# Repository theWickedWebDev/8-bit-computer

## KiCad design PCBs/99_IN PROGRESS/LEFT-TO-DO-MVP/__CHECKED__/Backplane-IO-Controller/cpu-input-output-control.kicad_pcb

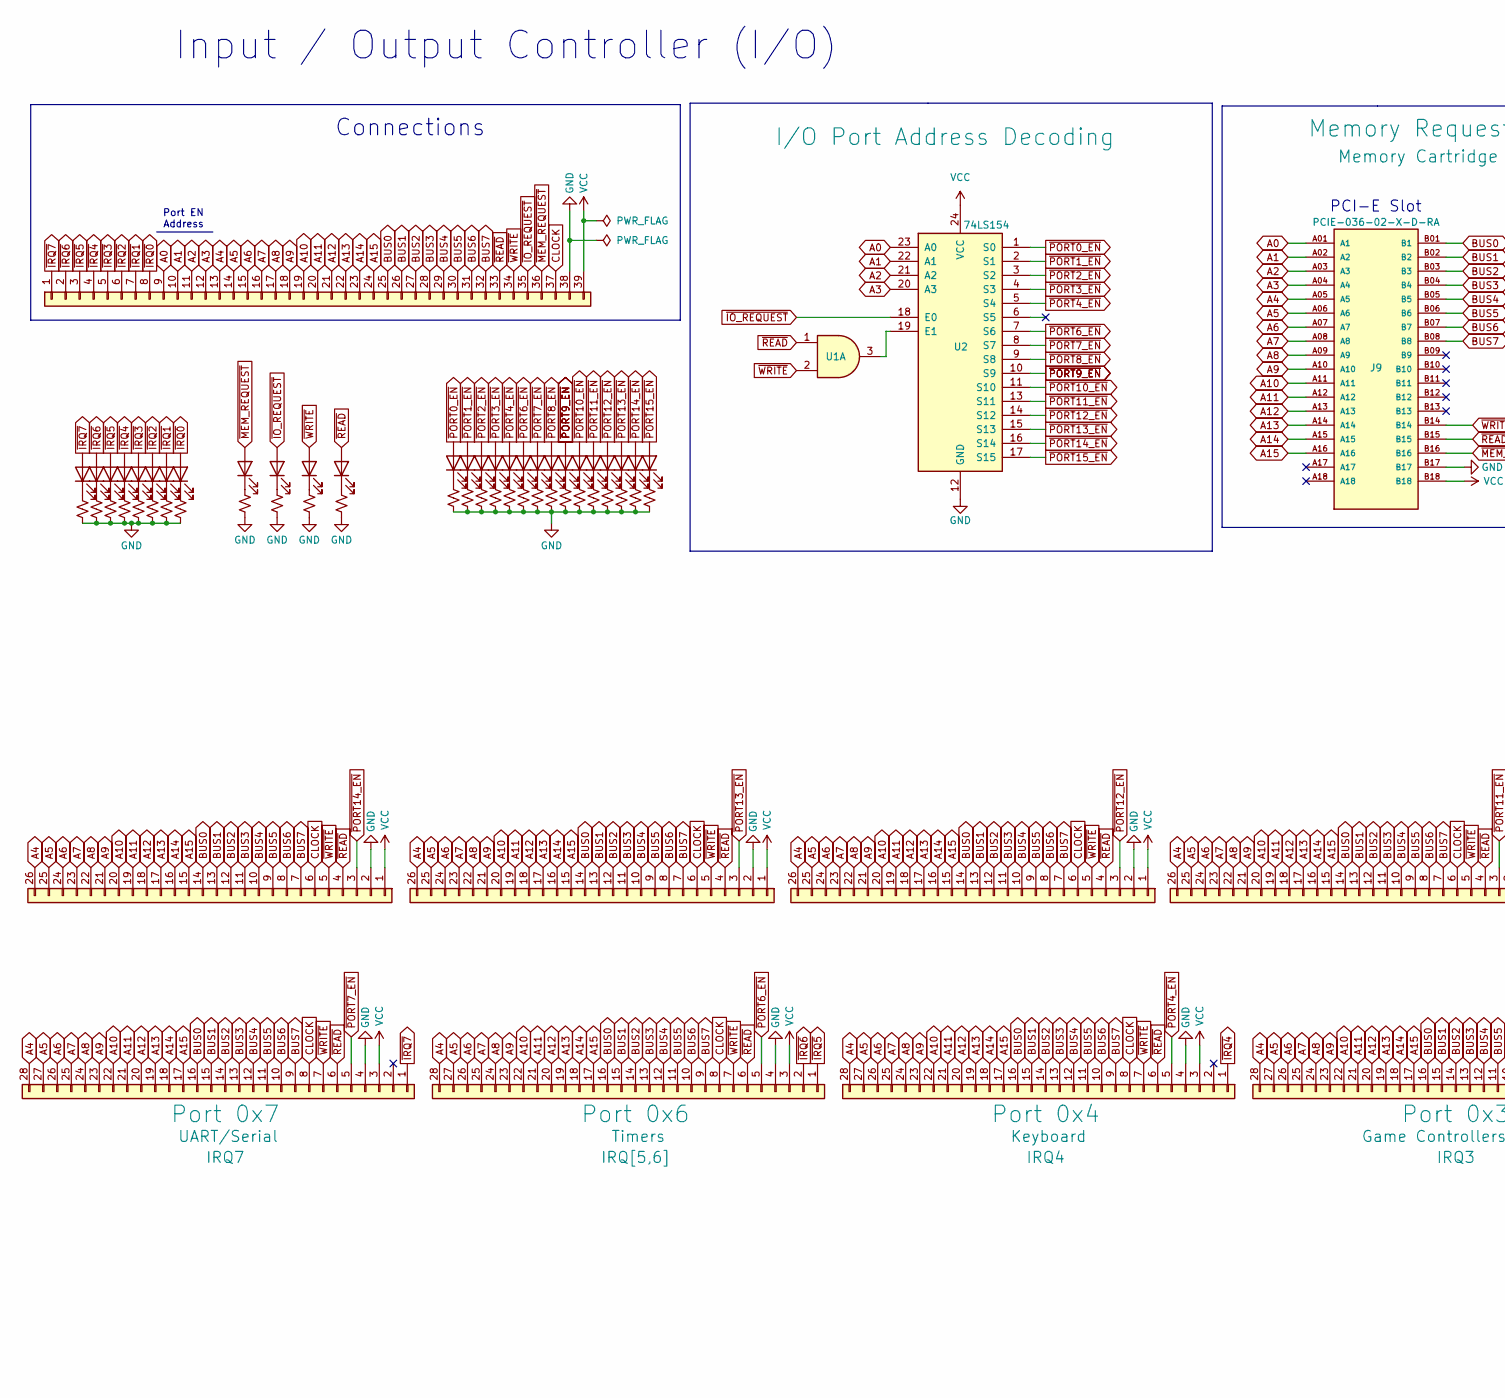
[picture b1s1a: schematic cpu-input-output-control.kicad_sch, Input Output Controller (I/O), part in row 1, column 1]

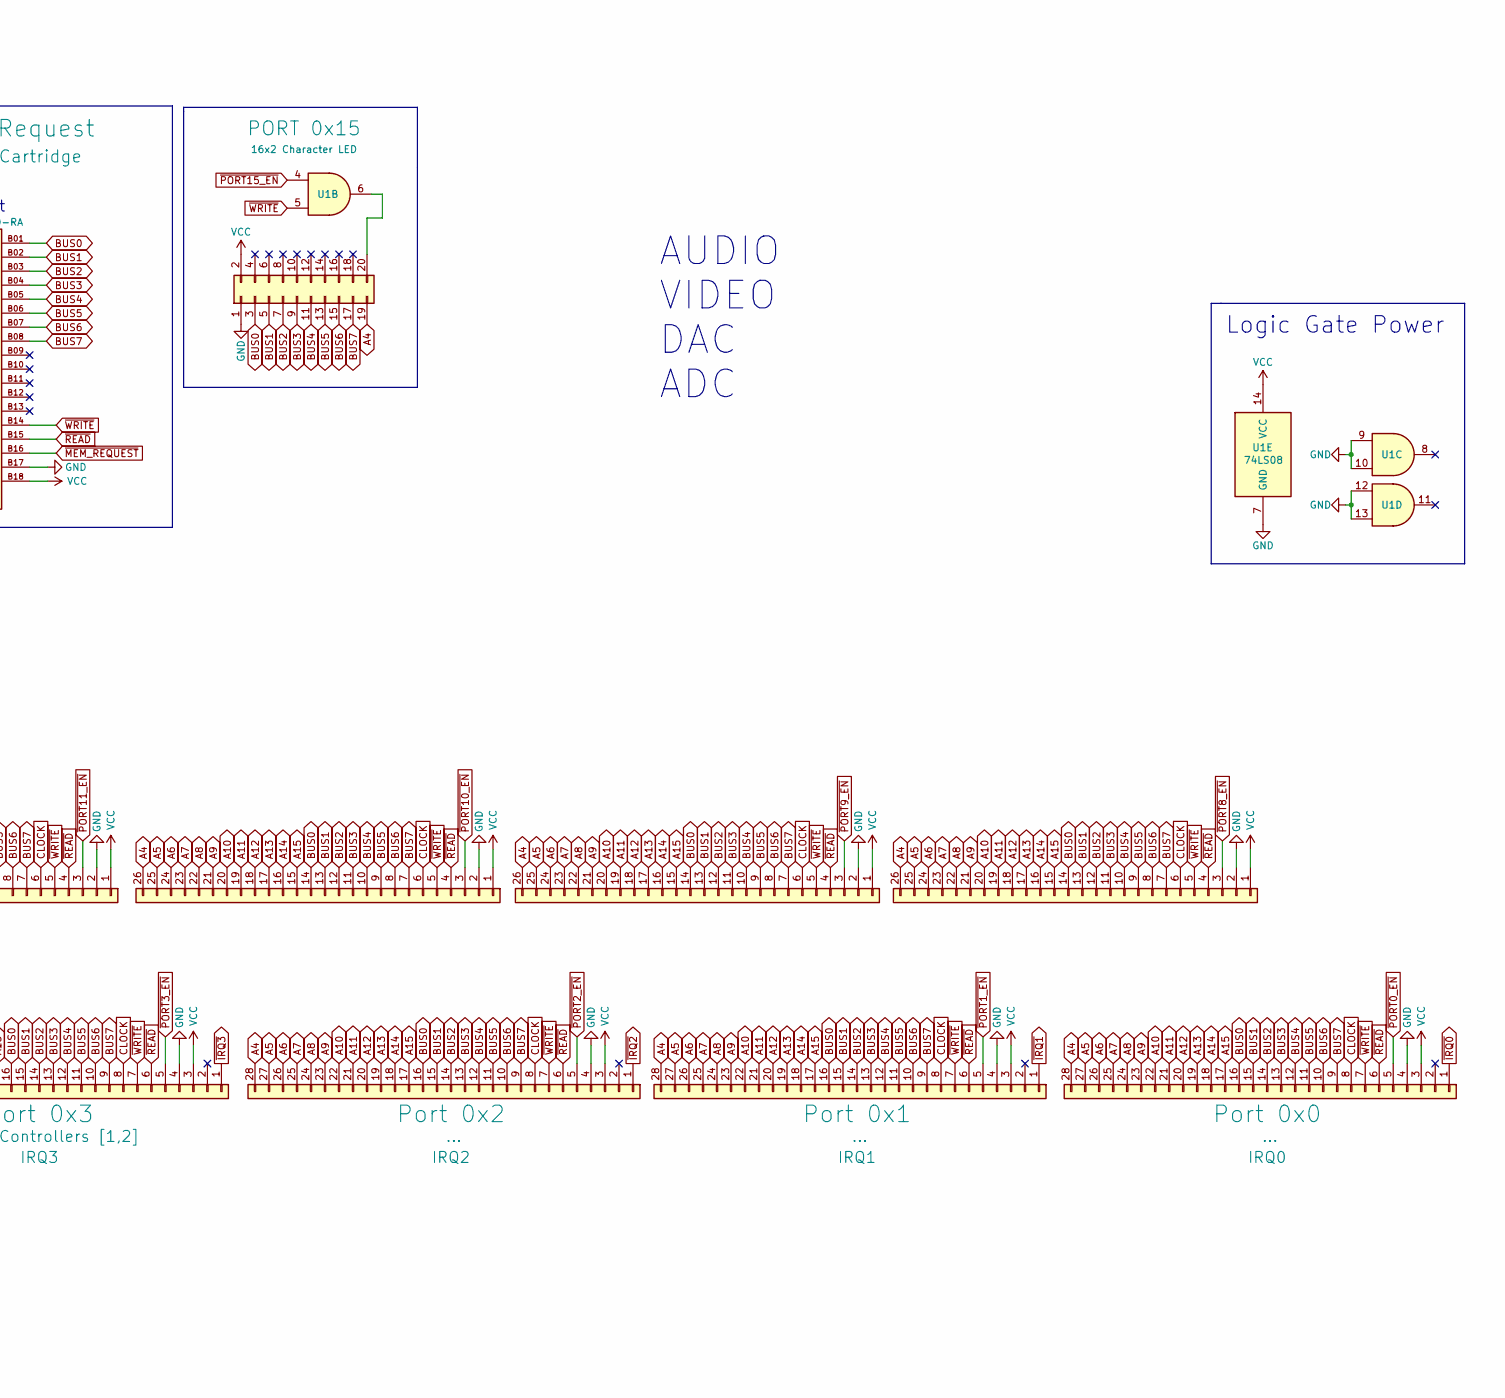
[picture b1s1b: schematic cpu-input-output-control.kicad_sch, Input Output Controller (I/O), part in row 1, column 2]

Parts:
D1, D2, D3, D4, D5, D6, D7, D8, D9, D10, D11, D12, D13, D14, D15, D16, D17, D18, D19, D20, D21, D22, D23, D24, D25, D26, D27: LED; LED_0805_2012Metric
J1, J4, J6, J8, J12, J14, J16: Conn_01x26; PinSocket_1x26_P2.54mm_Vertical
J2, J5, J7, J10, J13, J15, J17: Conn_01x28; PinSocket_1x28_P2.54mm_Vertical
J3: Conn_01x39; PinSocket_1x39_P2.54mm_Horizontal
J9: PCIE-036-02-X-D-RA; PCIE-036-Card-Slot-Connector; PARTREV D
J11: Conn_02x20_Odd_Even; IDC-Header_2x10_P2.54mm_Vertical
R1, R2, R3, R4, R5, R6, R7, R8, R9, R10, R11, R12, R13, R14, R15, R16, R17, R18, R19, R20, R21, R22, R23, R24, R25, R26, R27: R_Small_US; R_0805_2012Metric
U1: 74LS08; TSSOP-14_4.4x5mm_P0.65mm
U2: 74LS154; SO-24_5.3x15mm_P1.27mm

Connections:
A0: J3.9, J9.A01 (A1), U2.23 (A0)
A1: J3.10, J9.A02 (A2), U2.22 (A1)
A2: J3.11, J9.A03 (A3), U2.21 (A2)
A3: J3.12, J9.A04 (A4), U2.20 (A3)
A4: J1.26, J2.28, J3.13, J4.26, J5.28, J6.26, J7.28, J8.26, J9.A05 (A5), J10.28, J11.19, J12.26, J13.28, J14.26, J15.28, J16.26, J17.28
A5: J1.25, J2.27, J3.14, J4.25, J5.27, J6.25, J7.27, J8.25, J9.A06 (A6), J10.27, J12.25, J13.27, J14.25, J15.27, J16.25, J17.27
A6: J1.24, J2.26, J3.15, J4.24, J5.26, J6.24, J7.26, J8.24, J9.A07 (A7), J10.26, J12.24, J13.26, J14.24, J15.26, J16.24, J17.26
A7: J1.23, J2.25, J3.16, J4.23, J5.25, J6.23, J7.25, J8.23, J9.A08 (A8), J10.25, J12.23, J13.25, J14.23, J15.25, J16.23, J17.25
A8: J1.22, J2.24, J3.17, J4.22, J5.24, J6.22, J7.24, J8.22, J9.A09 (A9), J10.24, J12.22, J13.24, J14.22, J15.24, J16.22, J17.24
A9: J1.21, J2.23, J3.18, J4.21, J5.23, J6.21, J7.23, J8.21, J9.A10, J10.23, J12.21, J13.23, J14.21, J15.23, J16.21, J17.23
A10: J1.20, J2.22, J3.19, J4.20, J5.22, J6.20, J7.22, J8.20, J9.A11, J10.22, J12.20, J13.22, J14.20, J15.22, J16.20, J17.22
A11: J1.19, J2.21, J3.20, J4.19, J5.21, J6.19, J7.21, J8.19, J9.A12, J10.21, J12.19, J13.21, J14.19, J15.21, J16.19, J17.21
A12: J1.18, J2.20, J3.21, J4.18, J5.20, J6.18, J7.20, J8.18, J9.A13, J10.20, J12.18, J13.20, J14.18, J15.20, J16.18, J17.20
A13: J1.17, J2.19, J3.22, J4.17, J5.19, J6.17, J7.19, J8.17, J9.A14, J10.19, J12.17, J13.19, J14.17, J15.19, J16.17, J17.19
A14: J1.16, J2.18, J3.23, J4.16, J5.18, J6.16, J7.18, J8.16, J9.A15, J10.18, J12.16, J13.18, J14.16, J15.18, J16.16, J17.18
A15: J1.15, J2.17, J3.24, J4.15, J5.17, J6.15, J7.17, J8.15, J9.A16, J10.17, J12.15, J13.17, J14.15, J15.17, J16.15, J17.17
BUS0: J1.14, J2.16, J3.25, J4.14, J5.16, J6.14, J7.16, J8.14, J9.B01 (B1), J10.16, J11.3, J12.14, J13.16, J14.14, J15.16, J16.14, J17.16
BUS1: J1.13, J2.15, J3.26, J4.13, J5.15, J6.13, J7.15, J8.13, J9.B02 (B2), J10.15, J11.5, J12.13, J13.15, J14.13, J15.15, J16.13, J17.15
BUS2: J1.12, J2.14, J3.27, J4.12, J5.14, J6.12, J7.14, J8.12, J9.B03 (B3), J10.14, J11.7, J12.12, J13.14, J14.12, J15.14, J16.12, J17.14
BUS3: J1.11, J2.13, J3.28, J4.11, J5.13, J6.11, J7.13, J8.11, J9.B04 (B4), J10.13, J11.9, J12.11, J13.13, J14.11, J15.13, J16.11, J17.13
BUS4: J1.10, J2.12, J3.29, J4.10, J5.12, J6.10, J7.12, J8.10, J9.B05 (B5), J10.12, J11.11, J12.10, J13.12, J14.10, J15.12, J16.10, J17.12
BUS5: J1.9, J2.11, J3.30, J4.9, J5.11, J6.9, J7.11, J8.9, J9.B06 (B6), J10.11, J11.13, J12.9, J13.11, J14.9, J15.11, J16.9, J17.11
BUS6: J1.8, J2.10, J3.31, J4.8, J5.10, J6.8, J7.10, J8.8, J9.B07 (B7), J10.10, J11.15, J12.8, J13.10, J14.8, J15.10, J16.8, J17.10
BUS7: J1.7, J2.9, J3.32, J4.7, J5.9, J6.7, J7.9, J8.7, J9.B08 (B8), J10.9, J11.17, J12.7, J13.9, J14.7, J15.9, J16.7, J17.9
CLOCK: J1.6, J2.8, J3.37, J4.6, J5.8, J6.6, J7.8, J8.6, J10.8, J12.6, J13.8, J14.6, J15.8, J16.6, J17.8
GND: J1.2, J2.4, J3.38, J4.2, J5.4, J6.2, J7.4, J8.2, J9.B17, J10.4, J11.1, J12.2, J13.4, J14.2, J15.4, J16.2, J17.4, R1.2, R2.2, R3.2, R4.2, R5.2, R6.2, R7.2, R8.2, R9.2, R10.2, R11.2, R12.2, R13.2, R14.2, R15.2, R16.2, R17.2, R18.2, R19.2, R20.2, R21.2, R22.2, R23.2, R24.2, R25.2, R26.2, R27.2, U1.7 (GND), U1.9, U1.10, U1.12, U1.13, U2.12 (GND)
unnamed: D1.1 (K), R1.1
unnamed: D2.1 (K), R2.1
unnamed: D3.1 (K), R3.1
unnamed: D4.1 (K), R4.1
unnamed: D5.1 (K), R5.1
unnamed: D6.1 (K), R6.1
unnamed: D7.1 (K), R7.1
unnamed: D8.1 (K), R8.1
unnamed: D9.1 (K), R9.1
unnamed: D10.1 (K), R10.1
unnamed: D11.1 (K), R11.1
unnamed: D12.1 (K), R12.1
unnamed: D13.1 (K), R13.1
unnamed: D14.1 (K), R14.1
unnamed: D15.1 (K), R15.1
unnamed: D16.1 (K), R16.1
unnamed: D17.1 (K), R17.1
unnamed: D18.1 (K), R18.1
unnamed: D19.1 (K), R19.1
unnamed: D20.1 (K), R20.1
unnamed: D21.1 (K), R21.1
unnamed: D22.1 (K), R22.1
unnamed: D23.1 (K), R23.1
unnamed: D24.1 (K), R24.1
unnamed: D25.1 (K), R25.1
unnamed: D26.1 (K), R26.1
unnamed: D27.1 (K), R27.1
unnamed: J11.20, U1.6
unnamed: U1.3, U2.19 (E1)
VCC: J1.1, J2.3, J3.39, J4.1, J5.3, J6.1, J7.3, J8.1, J9.B18, J10.3, J11.2, J12.1, J13.3, J14.1, J15.3, J16.1, J17.3, U1.14 (VCC), U2.24 (VCC)
~IO_REQUEST: D10.2 (A), J3.35, U2.18 (E0)
~IRQ0: D8.2 (A), J3.8, J17.1
~IRQ1: D7.2 (A), J3.7, J15.1
~IRQ2: D6.2 (A), J3.6, J13.1
~IRQ3: D5.2 (A), J3.5, J10.1
~IRQ4: D4.2 (A), J3.4, J7.1
~IRQ5: D3.2 (A), J3.3, J5.1
~IRQ6: D2.2 (A), J3.2, J5.2
~IRQ7: D1.2 (A), J2.1, J3.1
~MEM_REQUEST: D9.2 (A), J3.36, J9.B16
~PORT0_EN: D13.2 (A), J17.5, U2.1 (S0)
~PORT1_EN: D14.2 (A), J15.5, U2.2 (S1)
~PORT2_EN: D15.2 (A), J13.5, U2.3 (S2)
~PORT3_EN: D16.2 (A), J10.5, U2.4 (S3)
~PORT4_EN: D17.2 (A), J7.5, U2.5 (S4)
~PORT6_EN: D18.2 (A), J5.5, U2.7 (S6)
~PORT7_EN: D19.2 (A), J2.5, U2.8 (S7)
~PORT8_EN: D20.2 (A), J16.3, U2.9 (S8)
~PORT9_EN: D21.2 (A), J14.3, U2.10 (S9)
~PORT10_EN: D22.2 (A), J12.3, U2.11 (S10)
~PORT11_EN: D23.2 (A), J8.3, U2.13 (S11)
~PORT12_EN: D24.2 (A), J6.3, U2.14 (S12)
~PORT13_EN: D25.2 (A), J4.3, U2.15 (S13)
~PORT14_EN: D26.2 (A), J1.3, U2.16 (S14)
~PORT15_EN: D27.2 (A), U1.4, U2.17 (S15)
~READ: D12.2 (A), J1.4, J2.6, J3.33, J4.4, J5.6, J6.4, J7.6, J8.4, J9.B15, J10.6, J12.4, J13.6, J14.4, J15.6, J16.4, J17.6, U1.1
~WRITE: D11.2 (A), J1.5, J2.7, J3.34, J4.5, J5.7, J6.5, J7.7, J8.5, J9.B14, J10.7, J12.5, J13.7, J14.5, J15.7, J16.5, J17.7, U1.2, U1.5

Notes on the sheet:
Connections
Logic Gate Power
Input / Output Controller (I/O)
PCI-E Slot
Port EN Address
UART/SERIAL Timer0 Timer1 KEYBOARD GAME CONTROLLER 1 GAME CONTROLLER 2
AUDIO VIDEO DAC ADC

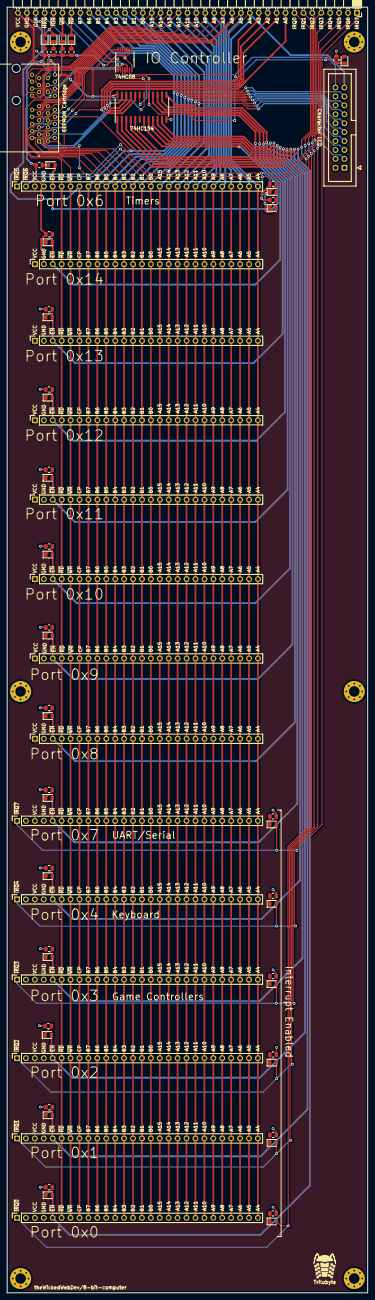
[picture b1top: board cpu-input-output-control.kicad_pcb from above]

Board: 2 copper layers, 102.6 x 366.0 mm, 73 parts (0 on the bottom side), 83 nets.

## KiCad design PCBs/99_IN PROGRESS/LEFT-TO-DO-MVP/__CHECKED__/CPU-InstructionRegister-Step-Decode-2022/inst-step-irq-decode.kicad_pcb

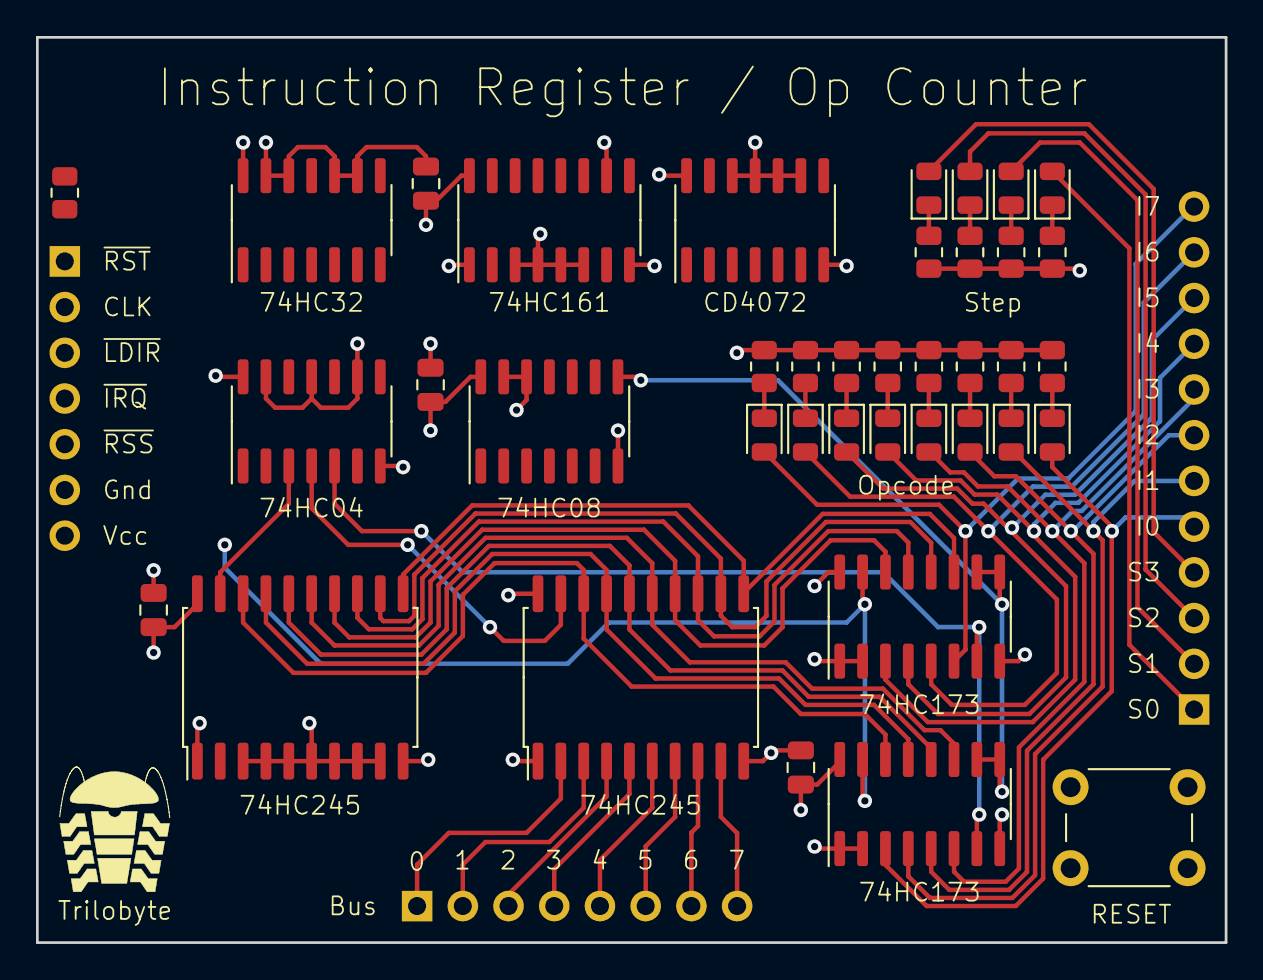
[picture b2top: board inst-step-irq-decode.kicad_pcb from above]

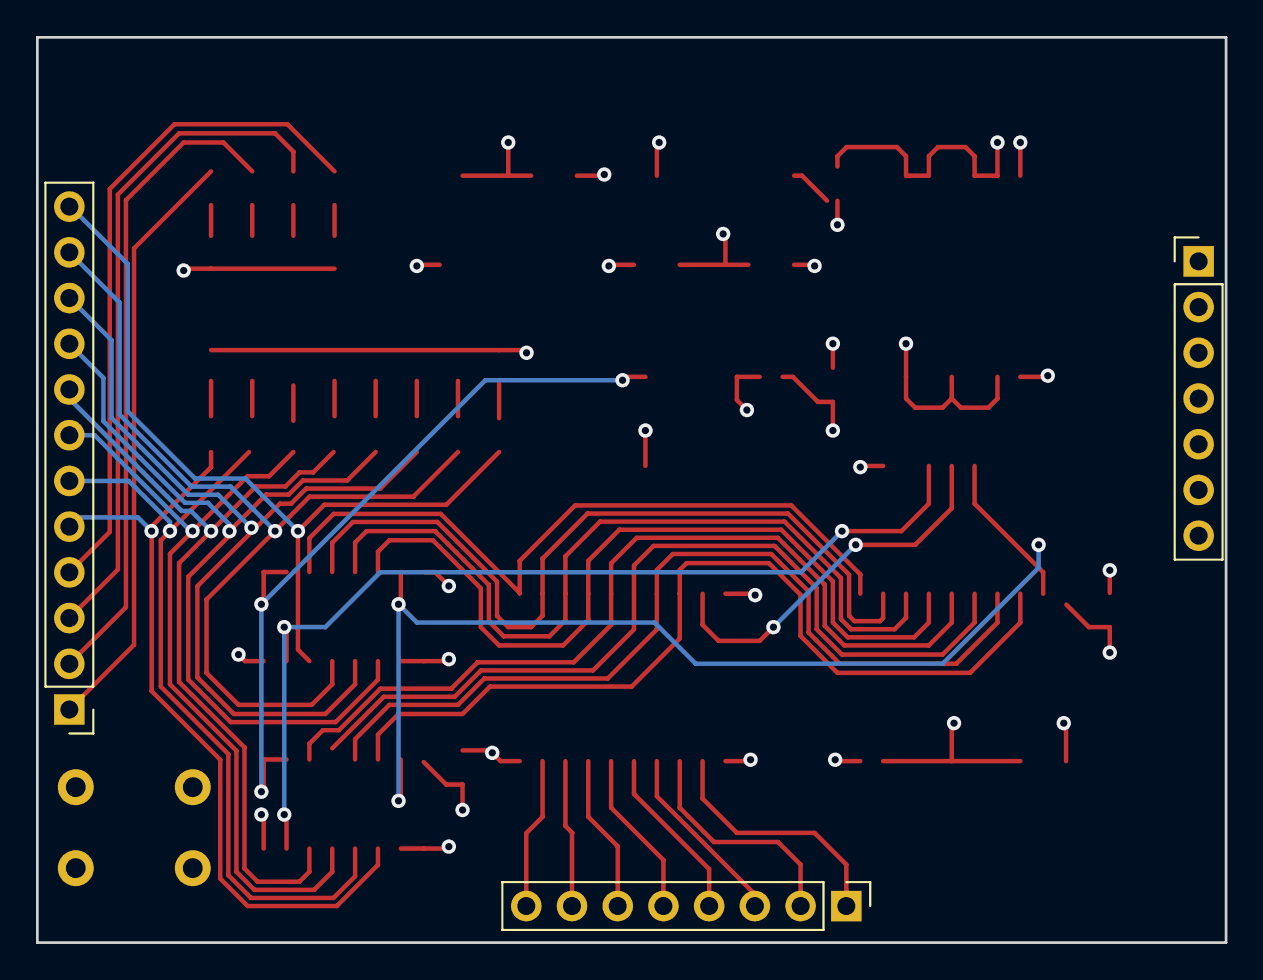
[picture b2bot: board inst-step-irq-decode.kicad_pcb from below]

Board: 4 copper layers, 66.0 x 50.3 mm, 42 parts (3 on the bottom side), 54 nets.

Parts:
C1, C2, C3, C4: C; C_0805_2012Metric
D1, D2, D3, D4, D5, D6, D7, D8, D9, D10, D11, D12: LED; LED_0805_2012Metric
J1: Conn_01x08; PinHeader_1x08_P2.54mm_Vertical
J2: Conn_01x12; PinHeader_1x12_P2.54mm_Vertical
J3: Conn_01x07; PinHeader_1x07_P2.54mm_Vertical
R1, R2, R3, R4, R5, R6, R7, R8, R9, R10, R11, R12, R13: R_Small_US; R_0805_2012Metric
SW1: SW_Push; SW_PUSH_6mm
U1: 74LS04; SOIC-14_3.9x8.7mm_P1.27mm
U2: 4072; SOIC-14_3.9x8.7mm_P1.27mm
U3: 74LS161; SOIC-16_3.9x9.9mm_P1.27mm
U4: 74LS32; SOIC-14_3.9x8.7mm_P1.27mm
U5: 74LS08; SOIC-14_3.9x8.7mm_P1.27mm
U6, U7: 74LS245; SOIC-20W_7.5x12.8mm_P1.27mm
U8, U9: 74LS173; SOIC-16_3.9x9.9mm_P1.27mm

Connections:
/INST_BUS_0: U6.18 (B0), U7.18 (B0), U8.14 (D0)
/INST_BUS_1: U6.17 (B1), U7.17 (B1), U8.13 (D1)
/INST_BUS_2: U6.16 (B2), U7.16 (B2), U8.12 (D2)
/INST_BUS_3: U6.15 (B3), U7.15 (B3), U8.11 (D3)
/INST_BUS_4: U6.14 (B4), U7.14 (B4), U9.14 (D0)
/INST_BUS_5: U6.13 (B5), U7.13 (B5), U9.13 (D1)
/INST_BUS_6: U6.12 (B6), U7.12 (B6), U9.12 (D2)
/INST_BUS_7: U6.11 (B7), U7.11 (B7), U9.11 (D3)
/~ZF: U2.1, U4.1, U4.5
BUS0: J1.1, U7.2 (A0)
BUS1: J1.2, U7.3 (A1)
BUS2: J1.3, U7.4 (A2)
BUS3: J1.4, U7.5 (A3)
BUS4: J1.5, U7.6 (A4)
BUS5: J1.6, U7.7 (A5)
BUS6: J1.7, U7.8 (A6)
BUS7: J1.8, U7.9 (A7)
CLOCK: J3.2, U1.5, U8.7 (Cp), U9.7 (Cp)
GND: C1.2, C2.2, C3.2, C4.2, J3.6, R2.2, R3.2, R4.2, R5.2, R6.2, R7.2, R8.2, R9.2, R10.2, R11.2, R12.2, R13.2, SW1.1, U1.1, U1.7 (GND), U1.9, U1.11, U1.13, U2.7 (VSS), U2.9, U2.10, U2.11, U2.12, U3.3 (D0), U3.4 (D1), U3.5 (D2), U3.6 (D3), U3.8 (GND), U4.7 (GND), U4.9, U4.10, U4.12, U4.13, U5.4, U5.5, U5.7 (GND), U5.12, U5.13, U6.10 (GND), U7.10 (GND), U8.1 (Oe1), U8.2 (Oe2), U8.8 (GND), U8.15 (Mr), U9.1 (Oe1), U9.2 (Oe2), U9.8 (GND), U9.15 (Mr)
INSTRUCTION0: D8.2 (A), J2.5, U8.3 (Q0)
INSTRUCTION1: D7.2 (A), J2.6, U8.4 (Q1)
INSTRUCTION2: D6.2 (A), J2.7, U8.5 (Q2)
INSTRUCTION3: D5.2 (A), J2.8, U8.6 (Q3)
INSTRUCTION4: D4.2 (A), J2.9, U9.3 (Q0)
INSTRUCTION5: D3.2 (A), J2.10, U9.4 (Q1)
INSTRUCTION6: D2.2 (A), J2.11, U9.5 (Q2)
INSTRUCTION7: D1.2 (A), J2.12, U9.6 (Q3)
unnamed: D1.1 (K), R2.1
unnamed: D2.1 (K), R3.1
unnamed: D3.1 (K), R4.1
unnamed: D4.1 (K), R5.1
unnamed: D5.1 (K), R6.1
unnamed: D6.1 (K), R7.1
unnamed: D7.1 (K), R8.1
unnamed: D8.1 (K), R9.1
unnamed: D9.1 (K), R10.1
unnamed: D10.1 (K), R11.1
unnamed: D11.1 (K), R12.1
unnamed: D12.1 (K), R13.1
unnamed: U1.4, U7.19 (CE)
unnamed: U1.6, U3.2 (CP)
unnamed: U4.3, U5.2
unnamed: U4.6, U5.1
unnamed: U5.8, U8.9 (E1), U8.10 (E2), U9.9 (E1), U9.10 (E2)
STEP0: D12.2 (A), J2.1, U2.2, U3.14 (Q0)
STEP1: D11.2 (A), J2.2, U2.3, U3.13 (Q1)
STEP2: D10.2 (A), J2.3, U2.4, U3.12 (Q2)
STEP3: D9.2 (A), J2.4, U2.5, U3.11 (Q3)
VCC: C1.1, C2.1, C3.1, C4.1, J3.7, R1.2, U1.14 (VCC), U2.14 (VDD), U3.1 (~MR), U3.7 (CEP), U3.10 (CET), U3.16 (VCC), U4.14 (VCC), U5.14 (VCC), U6.1 (A->B), U6.3 (A1), U6.4 (A2), U6.5 (A3), U6.6 (A4), U6.7 (A5), U6.8 (A6), U6.9 (A7), U6.20 (VCC), U7.1 (A->B), U7.20 (VCC), U8.16 (VCC), U9.16 (VCC)
~BUS_SEL: U1.3, U5.3, U5.9, U6.19 (CE)
~INT_REQUEST: J3.4, U4.4
~LD_IR: J3.3, U5.10
~RESET_STEP: J3.5, U3.9 (~PE)
~RESET: J3.1, R1.1, SW1.2, U4.2, U6.2 (A0)

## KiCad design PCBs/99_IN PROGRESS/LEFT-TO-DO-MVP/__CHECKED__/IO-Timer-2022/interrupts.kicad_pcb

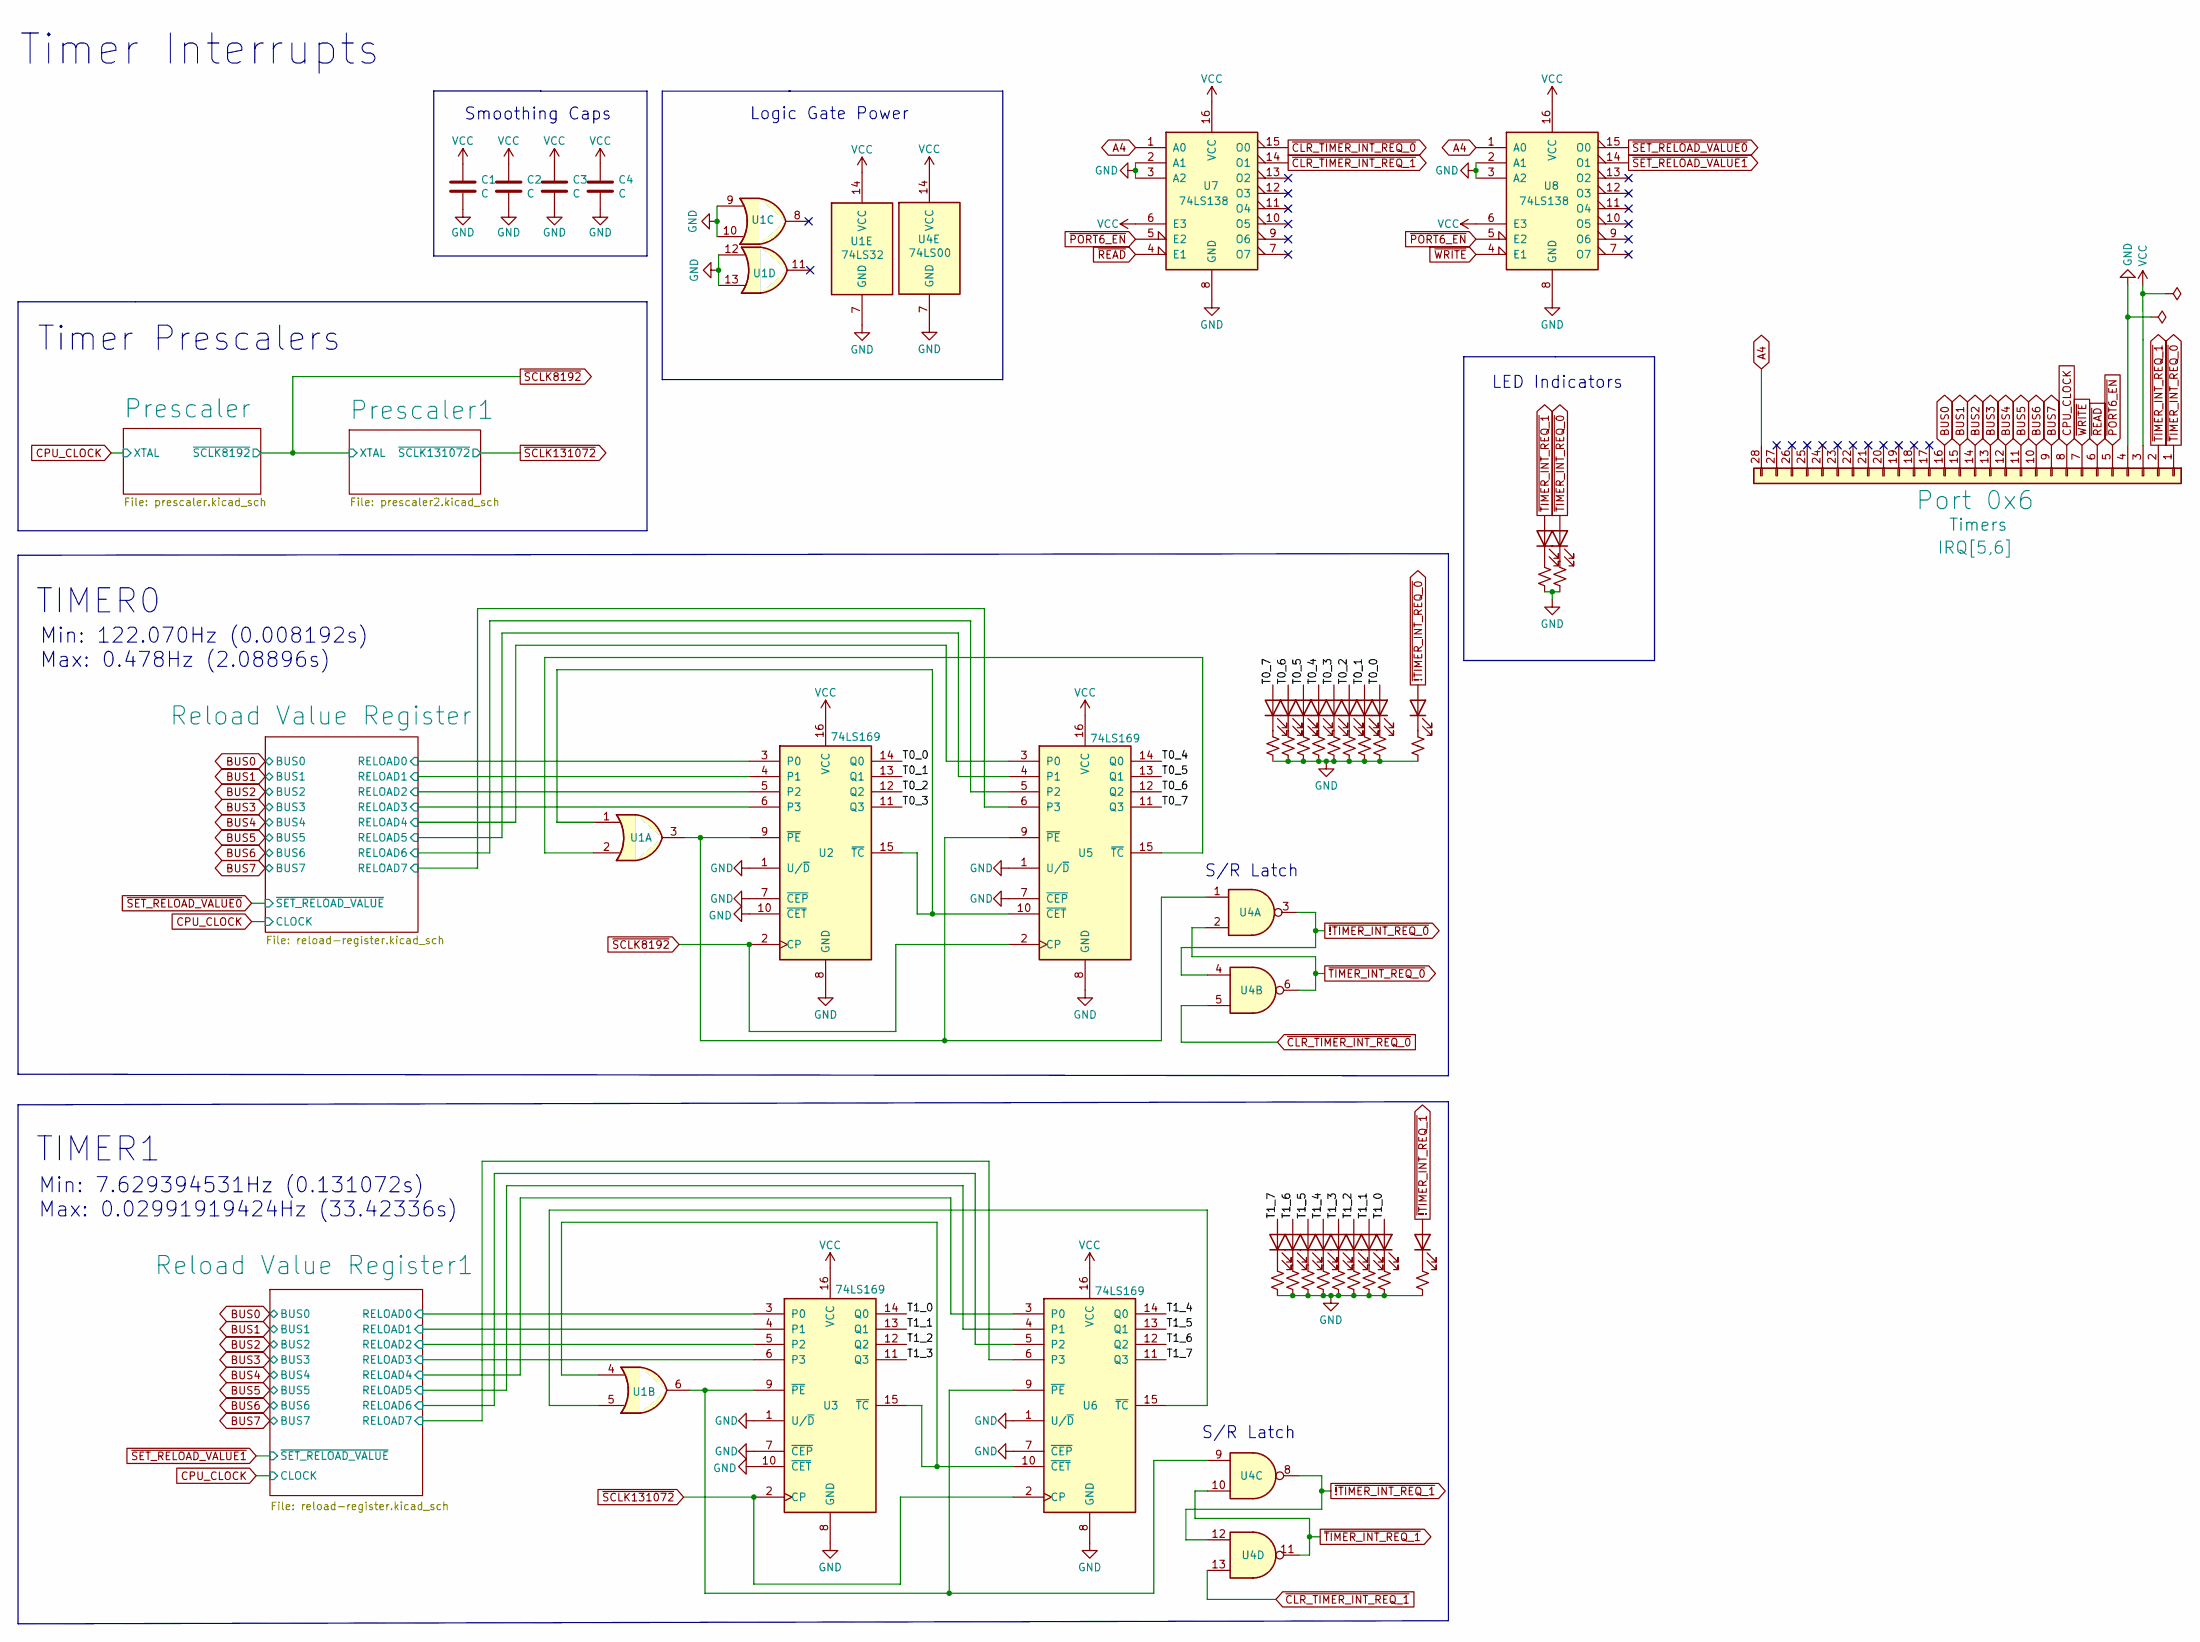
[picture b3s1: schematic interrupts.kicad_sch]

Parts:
C1, C2, C3, C4: C; C_0805_2012Metric
D1, D2, D3, D4, D5, D6, D7, D8, D9, D10, D11, D12, D13, D14, D15, D16, D17, D18, D19, D20: LED; LED_0805_2012Metric
J1: Conn_01x28; PinHeader_1x28_P2.54mm_Horizontal
R1, R2, R3, R4, R5, R6, R7, R8, R9, R10, R11, R12, R13, R14, R15, R16, R17, R18, R19, R20: R_Small_US; R_0805_2012Metric
U1: 74LS32
U2, U3, U5, U6: 74LS169; SOIC-16_3.9x9.9mm_P1.27mm
U4: 74LS00
U7, U8: 74LS138; SOIC-16_3.9x9.9mm_P1.27mm

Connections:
/Reload Value Register1/RELOAD0: U3.3 (P0); also elsewhere on the board
/Reload Value Register1/RELOAD1: U3.4 (P1); also elsewhere on the board
/Reload Value Register1/RELOAD2: U3.5 (P2); also elsewhere on the board
/Reload Value Register1/RELOAD3: U3.6 (P3); also elsewhere on the board
/Reload Value Register1/RELOAD4: U6.3 (P0); also elsewhere on the board
/Reload Value Register1/RELOAD5: U6.4 (P1); also elsewhere on the board
/Reload Value Register1/RELOAD6: U6.5 (P2); also elsewhere on the board
/Reload Value Register1/RELOAD7: U6.6 (P3); also elsewhere on the board
/Reload Value Register/RELOAD0: U2.3 (P0); also elsewhere on the board
/Reload Value Register/RELOAD1: U2.4 (P1); also elsewhere on the board
/Reload Value Register/RELOAD2: U2.5 (P2); also elsewhere on the board
/Reload Value Register/RELOAD3: U2.6 (P3); also elsewhere on the board
/Reload Value Register/RELOAD4: U5.3 (P0); also elsewhere on the board
/Reload Value Register/RELOAD5: U5.4 (P1); also elsewhere on the board
/Reload Value Register/RELOAD6: U5.5 (P2); also elsewhere on the board
/Reload Value Register/RELOAD7: U5.6 (P3); also elsewhere on the board
/T0_0: D15.2 (A), U2.14 (Q0)
/T0_1: D13.2 (A), U2.13 (Q1)
/T0_2: D11.2 (A), U2.12 (Q2)
/T0_3: D9.2 (A), U2.11 (Q3)
/T0_4: D7.2 (A), U5.14 (Q0)
/T0_5: D5.2 (A), U5.13 (Q1)
/T0_6: D3.2 (A), U5.12 (Q2)
/T0_7: D1.2 (A), U5.11 (Q3)
/T1_0: D16.2 (A), U3.14 (Q0)
/T1_1: D14.2 (A), U3.13 (Q1)
/T1_2: D12.2 (A), U3.12 (Q2)
/T1_3: D10.2 (A), U3.11 (Q3)
/T1_4: D8.2 (A), U6.14 (Q0)
/T1_5: D6.2 (A), U6.13 (Q1)
/T1_6: D4.2 (A), U6.12 (Q2)
/T1_7: D2.2 (A), U6.11 (Q3)
A4: J1.28, U7.1 (A0), U8.1 (A0)
BUS0: J1.16; also elsewhere on the board
BUS1: J1.15; also elsewhere on the board
BUS2: J1.14; also elsewhere on the board
BUS3: J1.13; also elsewhere on the board
BUS4: J1.12; also elsewhere on the board
BUS5: J1.11; also elsewhere on the board
BUS6: J1.10; also elsewhere on the board
BUS7: J1.9; also elsewhere on the board
CPU_CLOCK: J1.8; also elsewhere on the board
GND: C1.2, C2.2, C3.2, C4.2, J1.4, R1.2, R2.2, R3.2, R4.2, R5.2, R6.2, R7.2, R8.2, R9.2, R10.2, R11.2, R12.2, R13.2, R14.2, R15.2, R16.2, R17.2, R18.2, R19.2, R20.2, U1.7 (GND), U1.9, U1.10, U1.12, U1.13, U2.1 (U/~D), U2.7 (~CEP), U2.8 (GND), U2.10 (~CET), U3.1 (U/~D), U3.7 (~CEP), U3.8 (GND), U3.10 (~CET), U4.7 (GND), U5.1 (U/~D), U5.7 (~CEP), U5.8 (GND), U6.1 (U/~D), U6.7 (~CEP), U6.8 (GND), U7.2 (A1), U7.3 (A2), U7.8 (GND), U8.2 (A1), U8.3 (A2), U8.8 (GND); also elsewhere on the board
unnamed: D1.1 (K), R1.1
unnamed: D2.1 (K), R2.1
unnamed: D3.1 (K), R3.1
unnamed: D4.1 (K), R4.1
unnamed: D5.1 (K), R5.1
unnamed: D6.1 (K), R6.1
unnamed: D7.1 (K), R7.1
unnamed: D8.1 (K), R8.1
unnamed: D9.1 (K), R9.1
unnamed: D10.1 (K), R10.1
unnamed: D11.1 (K), R11.1
unnamed: D12.1 (K), R12.1
unnamed: D13.1 (K), R13.1
unnamed: D14.1 (K), R14.1
unnamed: D15.1 (K), R15.1
unnamed: D16.1 (K), R16.1
unnamed: D17.1 (K), R17.1
unnamed: D18.1 (K), R18.1
unnamed: D19.1 (K), R19.1
unnamed: D20.1 (K), R20.1
unnamed: U1.1, U2.15 (~TC), U5.10 (~CET)
unnamed: U1.2, U5.15 (~TC)
unnamed: U1.3, U2.9 (~PE), U4.1, U5.9 (~PE)
unnamed: U1.4, U3.15 (~TC), U6.10 (~CET)
unnamed: U1.5, U6.15 (~TC)
unnamed: U1.6, U3.9 (~PE), U4.9, U6.9 (~PE)
VCC: C1.1, C2.1, C3.1, C4.1, J1.3, U1.14 (VCC), U2.16 (VCC), U3.16 (VCC), U4.14 (VCC), U5.16 (VCC), U6.16 (VCC), U7.6 (E3), U7.16 (VCC), U8.6 (E3), U8.16 (VCC); also elsewhere on the board
~!TIMER_INT_REQ_0: D17.2 (A), U4.3, U4.4
~!TIMER_INT_REQ_1: D18.2 (A), U4.8, U4.12
~CLR_TIMER_INT_REQ_0: U4.5, U7.15 (O0)
~CLR_TIMER_INT_REQ_1: U4.13, U7.14 (O1)
~PORT6_EN: J1.5, U7.5 (E2), U8.5 (E2)
~READ: J1.6, U7.4 (E1)
~SCLK8192: U2.2 (CP), U5.2 (CP); also elsewhere on the board
~SCLK131072: U3.2 (CP), U6.2 (CP); also elsewhere on the board
~SET_RELOAD_VALUE0: U8.15 (O0); also elsewhere on the board
~SET_RELOAD_VALUE1: U8.14 (O1); also elsewhere on the board
~TIMER_INT_REQ_0: D20.2 (A), J1.1, U4.2, U4.6
~TIMER_INT_REQ_1: D19.2 (A), J1.2, U4.10, U4.11
~WRITE: J1.7, U8.4 (E1)

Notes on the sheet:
Min: 7.629394531Hz (0.131072s) Max: 0.02991919424Hz (33.42336s)
TIMER1
LED Indicators
Timer Interrupts
Timer Prescalers
Smoothing Caps
Logic Gate Power
S/R Latch
TIMER0
Min: 122.070Hz (0.008192s) Max: 0.478Hz (2.08896s)

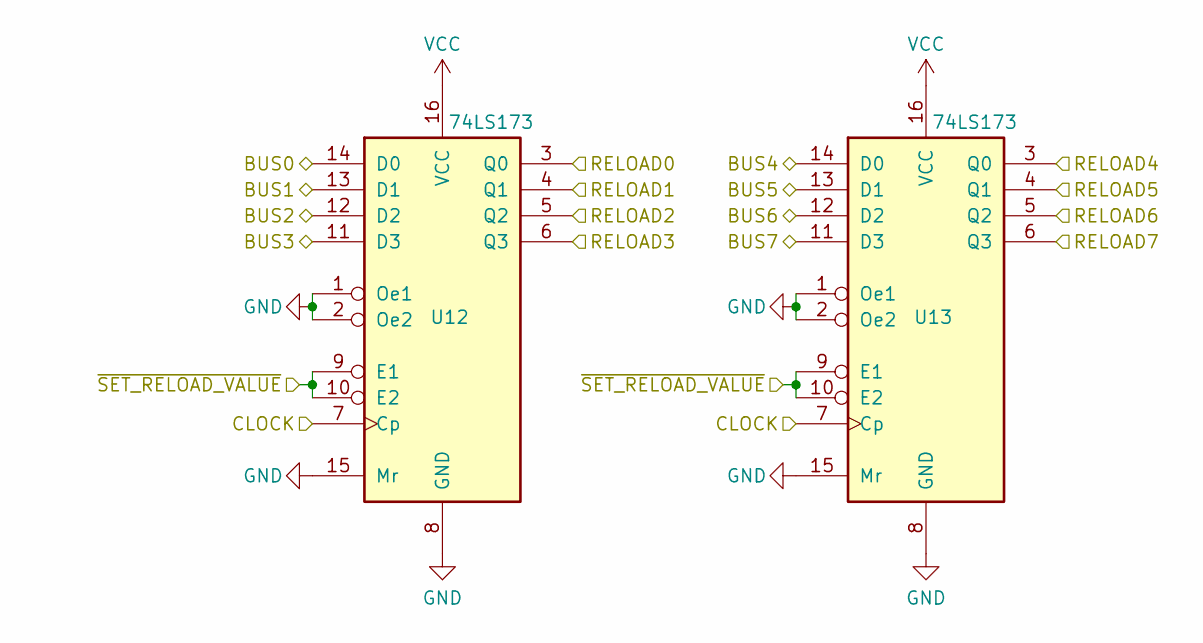
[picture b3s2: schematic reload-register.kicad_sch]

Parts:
U12, U13: 74LS173; SOIC-16_3.9x9.9mm_P1.27mm

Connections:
/Reload Value Register1/RELOAD0: U12.3 (Q0); also elsewhere on the board
/Reload Value Register1/RELOAD1: U12.4 (Q1); also elsewhere on the board
/Reload Value Register1/RELOAD2: U12.5 (Q2); also elsewhere on the board
/Reload Value Register1/RELOAD3: U12.6 (Q3); also elsewhere on the board
/Reload Value Register1/RELOAD4: U13.3 (Q0); also elsewhere on the board
/Reload Value Register1/RELOAD5: U13.4 (Q1); also elsewhere on the board
/Reload Value Register1/RELOAD6: U13.5 (Q2); also elsewhere on the board
/Reload Value Register1/RELOAD7: U13.6 (Q3); also elsewhere on the board
BUS0: U12.14 (D0); also elsewhere on the board
BUS1: U12.13 (D1); also elsewhere on the board
BUS2: U12.12 (D2); also elsewhere on the board
BUS3: U12.11 (D3); also elsewhere on the board
BUS4: U13.14 (D0); also elsewhere on the board
BUS5: U13.13 (D1); also elsewhere on the board
BUS6: U13.12 (D2); also elsewhere on the board
BUS7: U13.11 (D3); also elsewhere on the board
CPU_CLOCK: U12.7 (Cp), U13.7 (Cp); also elsewhere on the board
GND: U12.1 (Oe1), U12.2 (Oe2), U12.8 (GND), U12.15 (Mr), U13.1 (Oe1), U13.2 (Oe2), U13.8 (GND), U13.15 (Mr); also elsewhere on the board
VCC: U12.16 (VCC), U13.16 (VCC); also elsewhere on the board
~SET_RELOAD_VALUE1: U12.9 (E1), U12.10 (E2), U13.9 (E1), U13.10 (E2); also elsewhere on the board
